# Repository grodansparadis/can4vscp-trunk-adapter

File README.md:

# can4vscp-trunk-adapter

A CAN4VSCP trunk adapter for connected modules and adapters on a CAN4VSCP bus. You can use it for wired trunks and and use RJ45 connectors with standard CAT cable between nodes or wired cables if you prefer. It also have a DSUB with standard CAN pinout awth pin 9 optional connected to the power line to supported adapters that take power from the bus.

The schema looks lik this

KiCAD schema and pcb is in the kicad folder. The subfolder gerbers contains the production files.

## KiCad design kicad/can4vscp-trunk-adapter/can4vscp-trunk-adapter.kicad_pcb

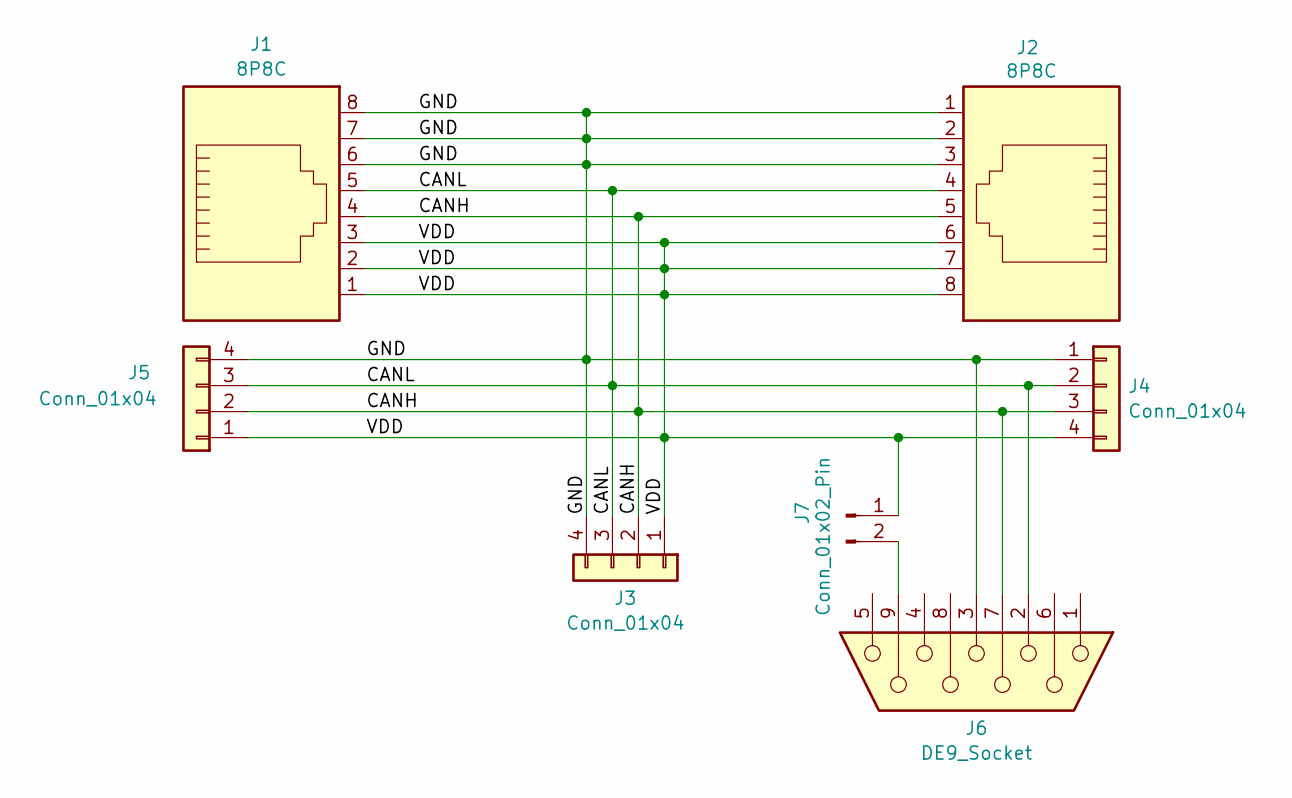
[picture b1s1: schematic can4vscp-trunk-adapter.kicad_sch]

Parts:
J1, J2: 8P8C; RJ45_Amphenol_54602-x08_Horizontal
J3, J4, J5: Conn_01x04; PhoenixContact_MC_1,5_4-G-3.81_1x04_P3.81mm_Horizontal
J6: DE9_Socket; DSUB-9_Pins_Vertical_P2.77x2.84mm
J7: Conn_01x02_Pin

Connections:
/CANH: J1.4, J2.5, J3.2, J4.3, J5.2, J6.7
/CANL: J1.5, J2.4, J3.3, J4.2, J5.3, J6.2
/GND: J1.6, J1.7, J1.8, J2.1, J2.2, J2.3, J3.4, J4.1, J5.4, J6.3
/VDD: J1.1, J1.2, J1.3, J2.6, J2.7, J2.8, J3.1, J4.4, J5.1, J7.1
unnamed: J6.9, J7.2

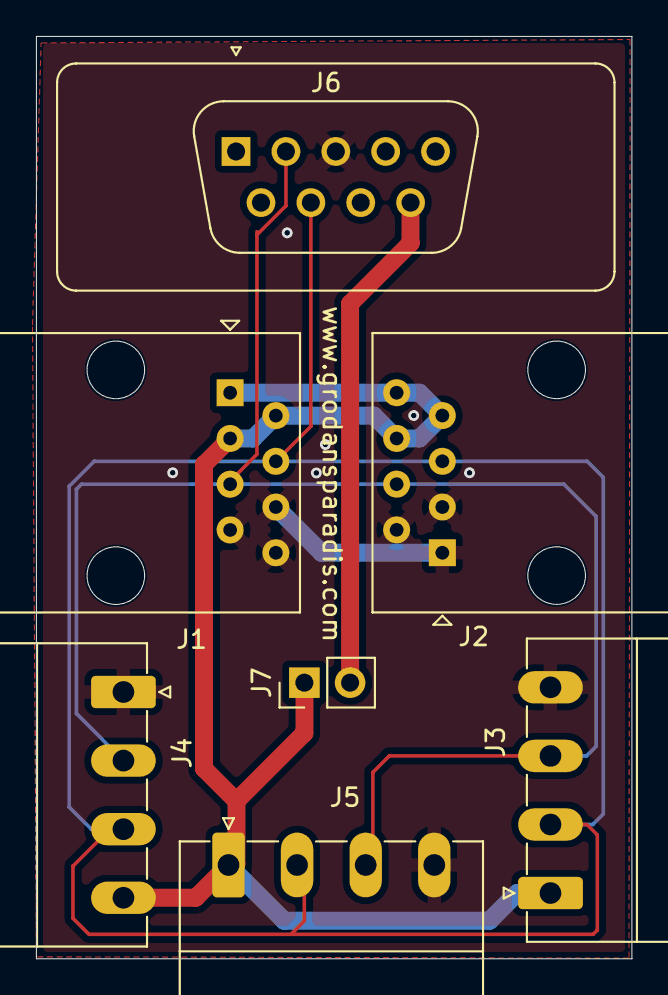
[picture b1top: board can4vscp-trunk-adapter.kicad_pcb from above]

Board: 2 copper layers, 33.1 x 51.2 mm, 7 parts (0 on the bottom side), 5 nets.

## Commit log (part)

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2026-04-24 Initial checkin
2026-05-04 Initial version
2026-05-05 Updated license to CERN
2026-06-03 Updated readme and addeschema and d pictures
